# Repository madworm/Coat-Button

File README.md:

Coat-Button
===========

LAYOUT FILES: Sewable blinky button for coats.

Make sure to check all branches!

You will find code for this project in [this](https://github.com/madworm/ATtiny_projects/tree/master/13/Coat-Button) repository.

---

Before having PC-boards made, please make sure you know about your manufacturer's peculiarities!
Especially drill-sizes and their tolerances may vary too much and give you trouble.

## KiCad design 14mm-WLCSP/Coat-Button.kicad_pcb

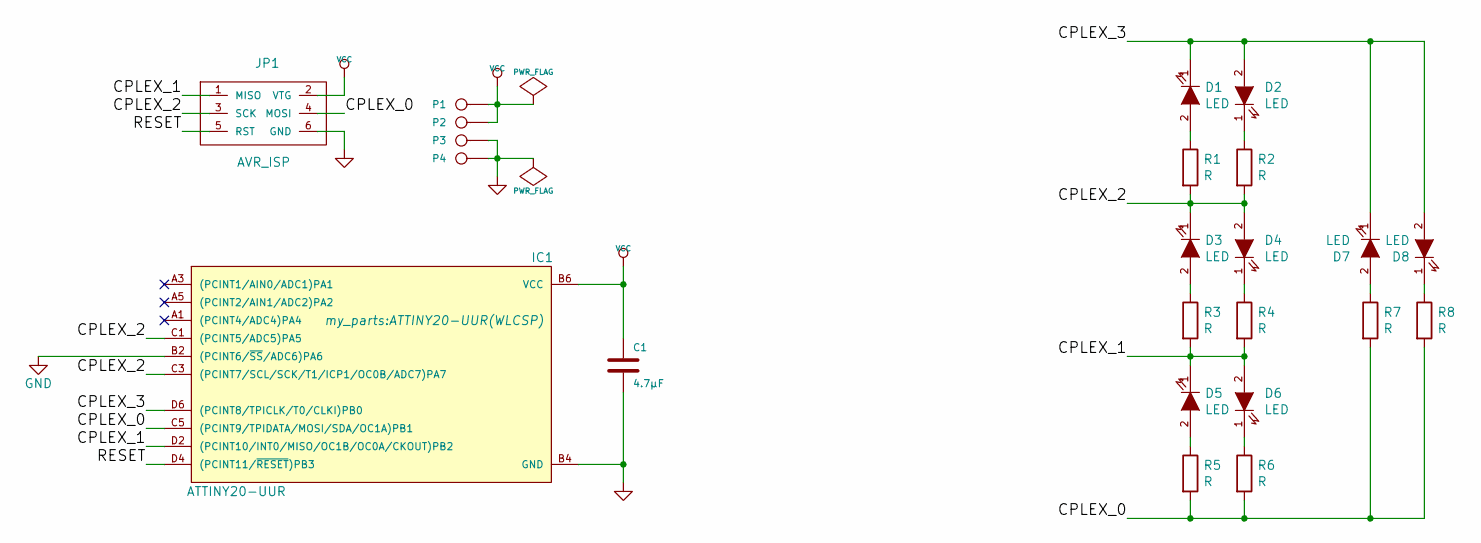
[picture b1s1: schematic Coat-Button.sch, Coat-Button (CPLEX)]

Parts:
C1: 4.7µF; MADW__C0805
D1, D2, D3, D4, D5, D6, D7, D8: LED; LED_0402
IC1: ATTINY20-UUR; ATTINY20-UUR(WLCSP)
JP1: AVR_ISP; DIL-3_1.27mm
P1, P2, P3, P4: CONN_1; SIL-1
R1, R2, R3, R4, R5, R6, R7, R8: R; R_0402

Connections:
/CPLEX_0: IC1.C5 ((PCINT9/TPIDATA/MOSI/SDA/OC1A)PB1), JP1.4 (MOSI), R5.2, R6.2, R7.2, R8.2
/CPLEX_1: D5.1 (K), D6.2 (A), IC1.D2 ((PCINT10/INT0/MISO/OC1B/OC0A/CKOUT)PB2), JP1.1 (MISO), R3.2, R4.2
/CPLEX_2: D3.1 (K), D4.2 (A), IC1.C1 ((PCINT5/ADC5)PA5), IC1.C3 ((PCINT7/SCL/SCK/T1/ICP1/OC0B/ADC7)PA7), JP1.3 (SCK), R1.2, R2.2
/CPLEX_3: D1.1 (K), D2.2 (A), D7.1 (K), D8.2 (A), IC1.D6 ((PCINT8/TPICLK/T0/CLKI)PB0)
/RESET: IC1.D4 ((PCINT11/~RESET~)PB3), JP1.5 (RST)
GND: C1.2, IC1.B2 ((PCINT6/~SS~/ADC6)PA6), IC1.B4 (GND), JP1.6 (GND), P3.1, P4.1
unnamed: D1.2 (A), R1.1
unnamed: D2.1 (K), R2.1
unnamed: D3.2 (A), R3.1
unnamed: D4.1 (K), R4.1
unnamed: D5.2 (A), R5.1
unnamed: D6.1 (K), R6.1
unnamed: D7.2 (A), R7.1
unnamed: D8.1 (K), R8.1
VCC: C1.1, IC1.B6 (VCC), JP1.2 (VTG), P1.1, P2.1

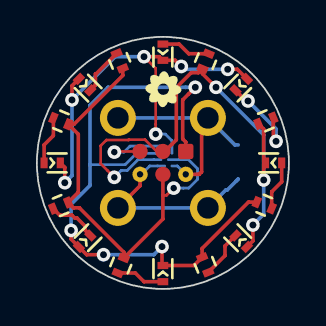
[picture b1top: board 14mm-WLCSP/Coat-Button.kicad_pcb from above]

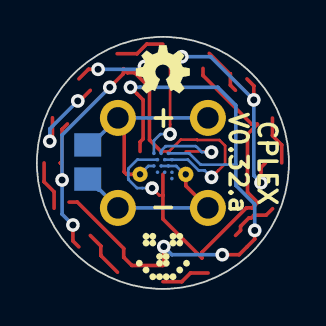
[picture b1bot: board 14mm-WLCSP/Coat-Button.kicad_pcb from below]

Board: 2 copper layers, 14.0 x 14.0 mm, 26 parts (4 on the bottom side), 15 nets.

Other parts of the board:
G1: OSHW-logo_silkscreen_3mm
G2: LED_smile_silkscreen_3mm
G3: floral-shape_silkscreen_2mm

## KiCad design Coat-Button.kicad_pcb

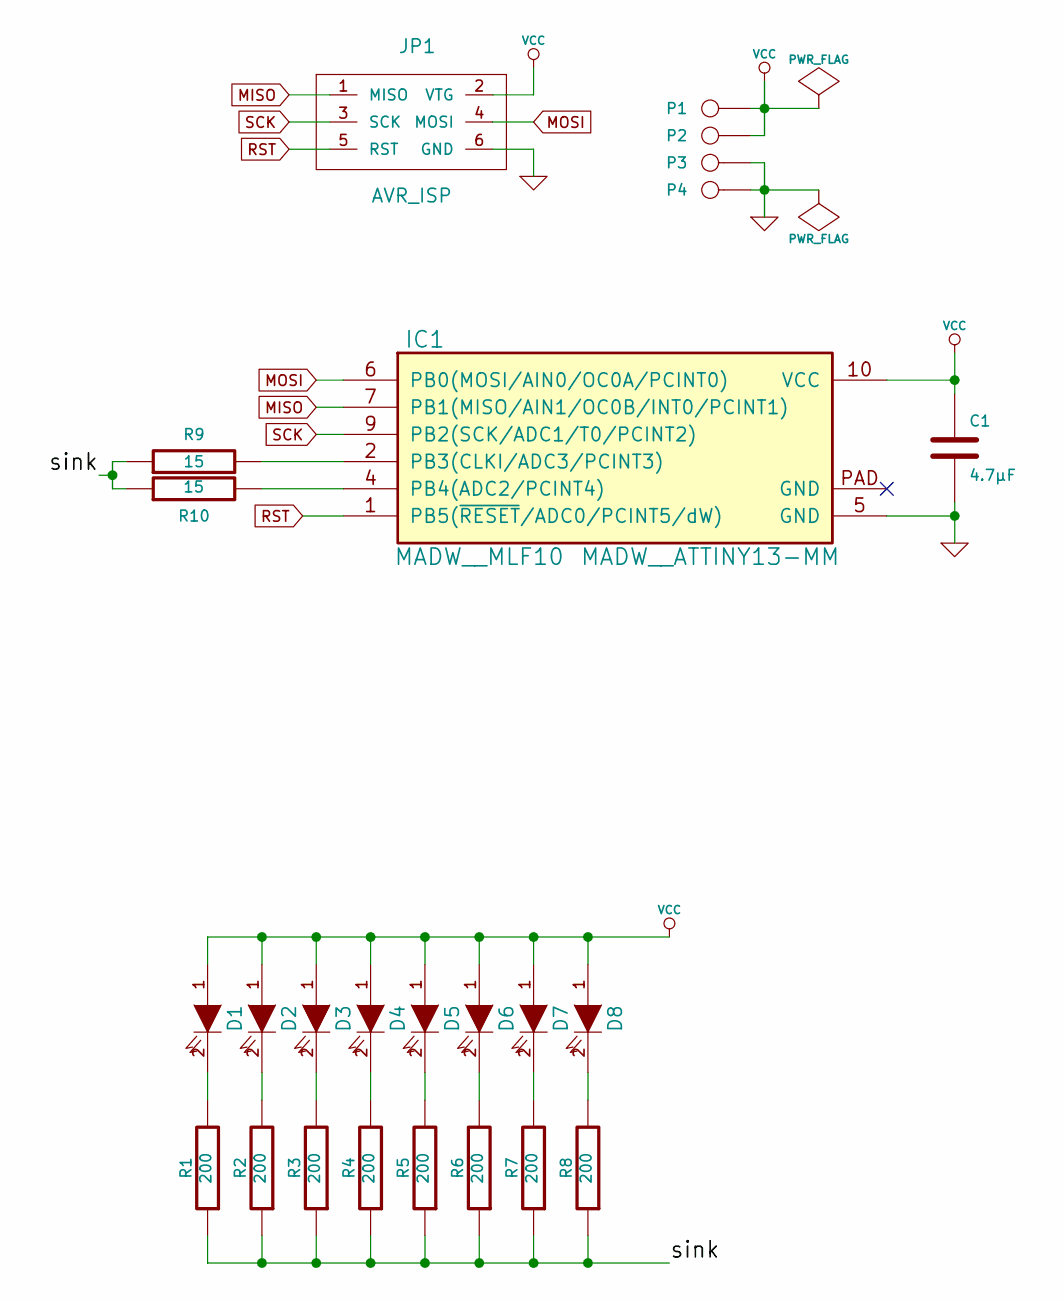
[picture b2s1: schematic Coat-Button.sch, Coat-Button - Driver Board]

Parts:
C1: 4.7µF
D1, D2, D3, D4, D5, D6, D7, D8: LED
IC1: MADW__ATTINY13-MM; MADW__MLF10
JP1: AVR_ISP
P1, P2, P3, P4: CONN_1
R1, R2, R3, R4, R5, R6, R7, R8: 200
R9, R10: 15

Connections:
/sink: R1.1, R2.1, R3.1, R4.1, R5.1, R6.1, R7.1, R8.1, R9.1, R10.1
GND: C1.2, IC1.5 (GND), JP1.6 (GND), P3.1, P4.1
MISO: IC1.7 (PB1(MISO/AIN1/OC0B/INT0/PCINT1)), JP1.1 (MISO)
MOSI: IC1.6 (PB0(MOSI/AIN0/OC0A/PCINT0)), JP1.4 (MOSI)
unnamed: IC1.2 (PB3(CLKI/ADC3/PCINT3)), R9.2
unnamed: IC1.4 (PB4(ADC2/PCINT4)), R10.2
unnamed: D3.2 (K), R3.2
unnamed: D4.2 (K), R4.2
unnamed: D5.2 (K), R5.2
unnamed: D6.2 (K), R6.2
unnamed: D7.2 (K), R7.2
unnamed: D8.2 (K), R8.2
unnamed: D1.2 (K), R1.2
unnamed: D2.2 (K), R2.2
RST: IC1.1 (PB5(~RESET~/ADC0/PCINT5/dW)), JP1.5 (RST)
SCK: IC1.9 (PB2(SCK/ADC1/T0/PCINT2)), JP1.3 (SCK)
VCC: C1.1, D1.1 (A), D2.1 (A), D3.1 (A), D4.1 (A), D5.1 (A), D6.1 (A), D7.1 (A), D8.1 (A), IC1.10 (VCC), JP1.2 (VTG), P1.1, P2.1

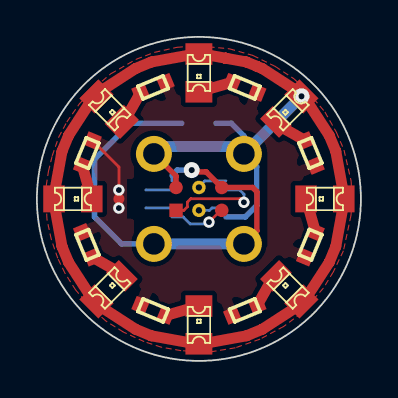
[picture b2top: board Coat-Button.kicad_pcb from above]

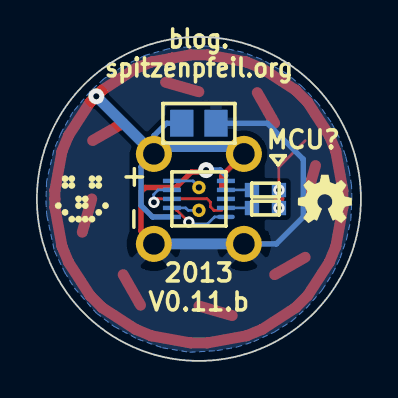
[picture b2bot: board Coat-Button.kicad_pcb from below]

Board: 2 copper layers, 18.0 x 18.0 mm, 25 parts (4 on the bottom side), 17 nets.

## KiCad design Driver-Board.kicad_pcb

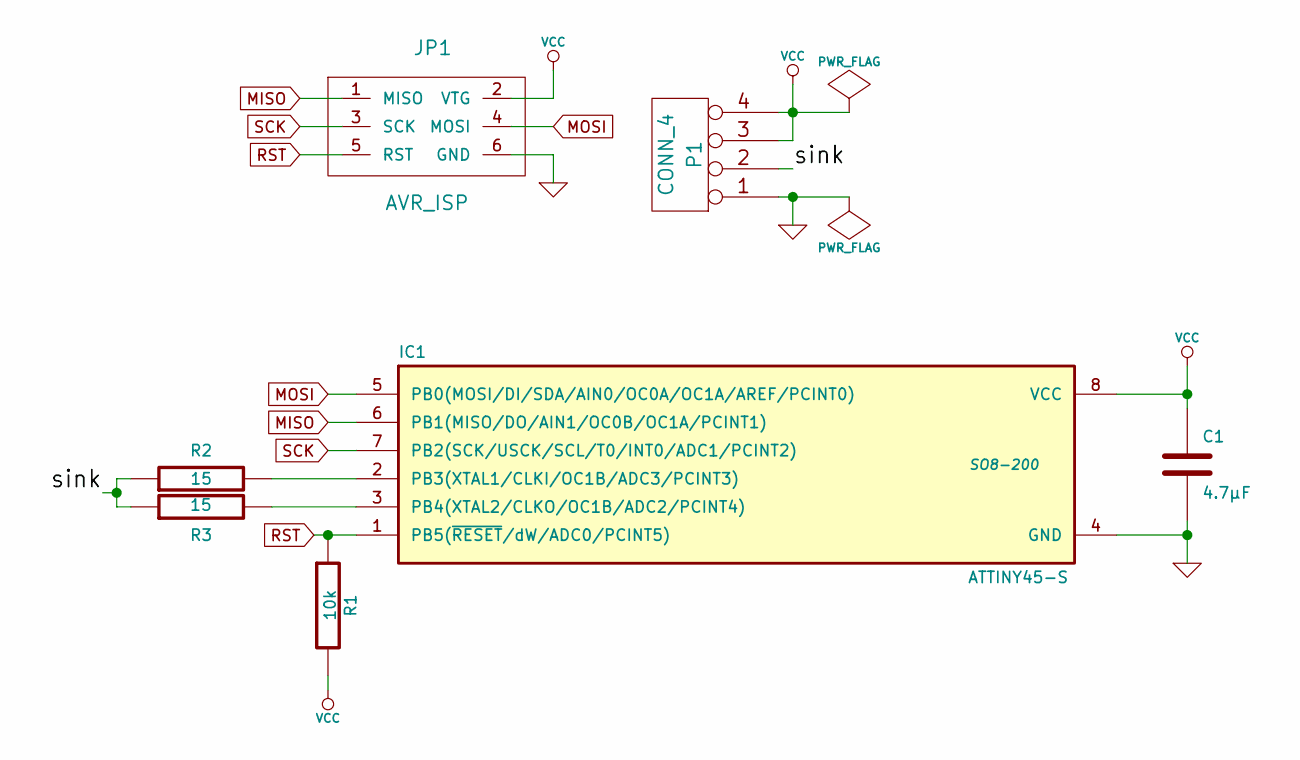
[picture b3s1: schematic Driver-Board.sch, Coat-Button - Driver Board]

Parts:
C1: 4.7µF
IC1: ATTINY45-S; SO8-200
JP1: AVR_ISP
P1: CONN_4
R1: 10k
R2, R3: 15

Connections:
/sink: P1.2, R2.1, R3.1
GND: C1.2, IC1.4 (GND), JP1.6 (GND), P1.1
MISO: IC1.6 (PB1(MISO/DO/AIN1/OC0B/OC1A/PCINT1)), JP1.1 (MISO)
MOSI: IC1.5 (PB0(MOSI/DI/SDA/AIN0/OC0A/OC1A/AREF/PCI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), JP1.4 (MOSI)
unnamed: IC1.3 (PB4(XTAL2/CLKO/OC1B/ADC2/PCINT4)), R3.2
unnamed: IC1.2 (PB3(XTAL1/CLKI/OC1B/ADC3/PCINT3)), R2.2
RST: IC1.1 (PB5(~RESET~/dW/ADC0/PCINT5)), JP1.5 (RST), R1.1
SCK: IC1.7 (PB2(SCK/USCK/SCL/T0/INT0/ADC1/PCINT2)), JP1.3 (SCK)
VCC: C1.1, IC1.8 (VCC), JP1.2 (VTG), P1.3, P1.4, R1.2

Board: 2 copper layers, 7 parts (0 on the bottom side), 9 nets, no tracks yet.

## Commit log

2013-09-14 On-board ATtiny13 wasn't doable. Not enough space.
2013-09-14 Created some PNGs.
2013-09-14 Added some stuff to the 'Driver-Board'.
2013-09-14 Added mechanical dimension.
2013-09-15 Managed to get an ATtiny13 (DFN10) on there again ;-)
2013-09-16 Tweaks. Added solder-bridge if no micro is used.
2013-09-18 Renamed stuff.
2013-09-18 Found & fixed a little pad-size inconsistency.
2013-09-18 Updated 'README.md'.
2013-09-18 Silkscreen tweaks.
2013-09-19 Updated dimensions info.
2013-09-19 Tweaks for viewing gerber files with gerbv.
2013-09-19 Forgot to set REFs for silkscreen logos.
2013-09-19 Some silkscreen / mask tweaks on the back side.
2013-09-23 Tweaks + schematic as pdf.
2013-09-23 Made one with dual-colour LEDs (0805). Just to see if possible.
    Had to use 0402 resitors...
2013-09-25 Moved some vias around.
    Tracks connecting to them were erroneously deleted by applying
    'Delete unconnected tracks'. Now everything is 'solid'.
2013-09-25 Added a SOT523 n-ch mosfet.
2013-09-25 Added 2 SOT523 n-ch mosfets + reduced LED resistors.
2013-09-27 Tweaked some vias.
2013-10-03 Modified the SOT523 footprint to allow easy bridging of drain/source.
2013-10-03 Tweaked SOT523 footprint (backside) for easy drain/source bridging.
    Now the same board can be used for single/dual color or just LEDs.
2013-10-03 Tweaked the BI-LED footprints a bit. Better for normal LEDs.
2013-10-03 Added alternative 0603 R. footprints for single-color mode.
2013-10-08 Added a bit of silkscreen art.
2013-10-12 Added 3D footprints. Looks good with new 3D viewer.
2013-10-12 Fixed 180° rotation of 0805 LED 3D models.
2013-10-14 Modified SOT523 footprints to allow easier solder bridges.
2013-10-14 Tweaked changes in previous commit.
2013-10-14 Moved capacitor + tweaks.
2014-01-15 Adjustments due to pcbnew's library manager.
2014-07-31 Added a comment to the schematic (LED resistors).
2014-07-31 Added simplified BOM file.
2014-08-21 Added 'Coat-Button__QSG' (quick start guide).
2016-04-07 Getting started with charlieplexing.
2016-04-08 Might be ready for ordering a prototype from oshpark.
2016-04-15 Added '14mm' board.
2016-04-25 Added '14mm-WLCSP' (ATtiny20-UUR).
